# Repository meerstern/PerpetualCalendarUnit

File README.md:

# 万年カレンダーユニット　Perpetual Calendar Unit

## 概要 
  * 2.13インチ、122x250 超低消費電力LCDを用いた万年カレンダーユニットです  
  * 現在の日付、時刻、その月を表示します  
  * 精度±3.8ppmの温度補正機能付RTC SD3077を搭載しています  
  * LCD横のジョイスティックで翌月や前月等、表示月を変更することが可能です  
  * 単三電池2本で約1年前後の電池寿命です  
  * Pico-SDKを使用したソースコードを公開しています  

## 仕様  
  * ジョイスティック(カレンダー切替、時刻合わせ)、BOOTボタン、RESETボタンを搭載しています  
  * マイコンRP2040、RTC SD3077、電源管理IC XC6194を使用しています  
  * RTCのINT信号によって電源管理ICからマイコンを1分に1回、起動させています  
  * 起動後はLCD表示を更新後、シャットダウン信号を電源管理ICに送って、マイコンの電源を切ることで省電力化しています    
  * RTCのINTとジョイスティックの中央ボタンは同一信号となっており、ユーザ操作の長押しによって復帰します  
  * 単三電池2本もしくはUSB電源(USB Type-C)  
  * 時刻(RTC)保持電池 CR1220  
  * サイズ82mm x32mm x 30mm(突起部、USBコネクタ除く)

## 注意点
  * LCDはガラス製のため、強い力や衝撃を与えると破損する可能性があります     
  * 使用時はクリップ等の金属がユニット内に入り込まないように注意してください  
  * 電池寿命は使用環境や使用方法によって大きく変動するため、期間を保証するものではありません  
  * 操作時はジョイスティックの中央を3秒程度長押しして、スリープから復帰させてください  
  * ジョイスティックの応答がない場合は背面のRSTボタンを押してください  
  * 万一、画面端に点表示が残る場合はカレンダー切替等で画面を数回リフレッシュすることで解消します  
  * 告知なしに部品や仕様を変更する場合があります  
  
## 使い方  

### a.通常使用の場合  
 単三電池2個もしくはUSB Type-CをUSB電源等に接続してください  
 画面がすぐに表示されない場合はLCD右横のジョイスティックの中央を3秒程度長押ししてください  
 万一、画面端に点表示が残る場合はカレンダー切替等で画面を数回リフレッシュすることで解消します  

### b.カレンダー切替  
 ジョイスティックの中央を3秒程度長押しして、スリープから復帰させてください  
 スリープから復帰すると画面が一瞬、点滅してLCDが再度、更新されます  
 この状態でジョイスティックを上下に動かすと表示月を切り替えることが可能です  
 10秒以上放置するか、ジョイスティックの中央を再度、押すと現在の月に戻ります  
 万一、ジョイスティックの応答がない場合は背面のRSTボタンを押してください  
　
### c.日付時刻合わせ  
 ジョイスティックの中央を3秒程度長押しして、スリープから復帰させてください  
 スリープから復帰すると画面が一瞬、点滅してLCDが再度、更新されます  
 この状態でジョイスティックを左右どちらかに3秒程度長押しすると日付、時刻合わせモードに入ります  
 左右で設定項目変更、上下で数値を変更します  
 決定する場合ははジョイスティックの中央を押して設定を完了させます  
 万一、ジョイスティックの応答がない場合は背面のRSTボタンを押してください  
    
### d.ファームウェアの書換を行う場合
 PC等にUSB Type-Cを接続し、BOOTボタンを押した状態でRSTボタンを押すとUSBドライブとして認識されます  
 ファームウェアファイル(*.uf2)を認識されたUSBドライブに書き込むことでファームの書換が可能です  
 
## リリースノート
　v1.1 クロックダウンによる更なる省エネ化を実施  
　v1.2 初期状態によってスリープ復帰に失敗する不具合を修正  

## 電池交換時の確認
  * RTC電池は電源供給なしで3年以上、日時、時刻を保持することが可能です  
  * 万一、保持できなくなった場合はCR1220の電池交換を行ってください  
  * 電池交換後は日時、時刻が不定値となるため、必ず時刻、日付を再設定してください  

## 外観

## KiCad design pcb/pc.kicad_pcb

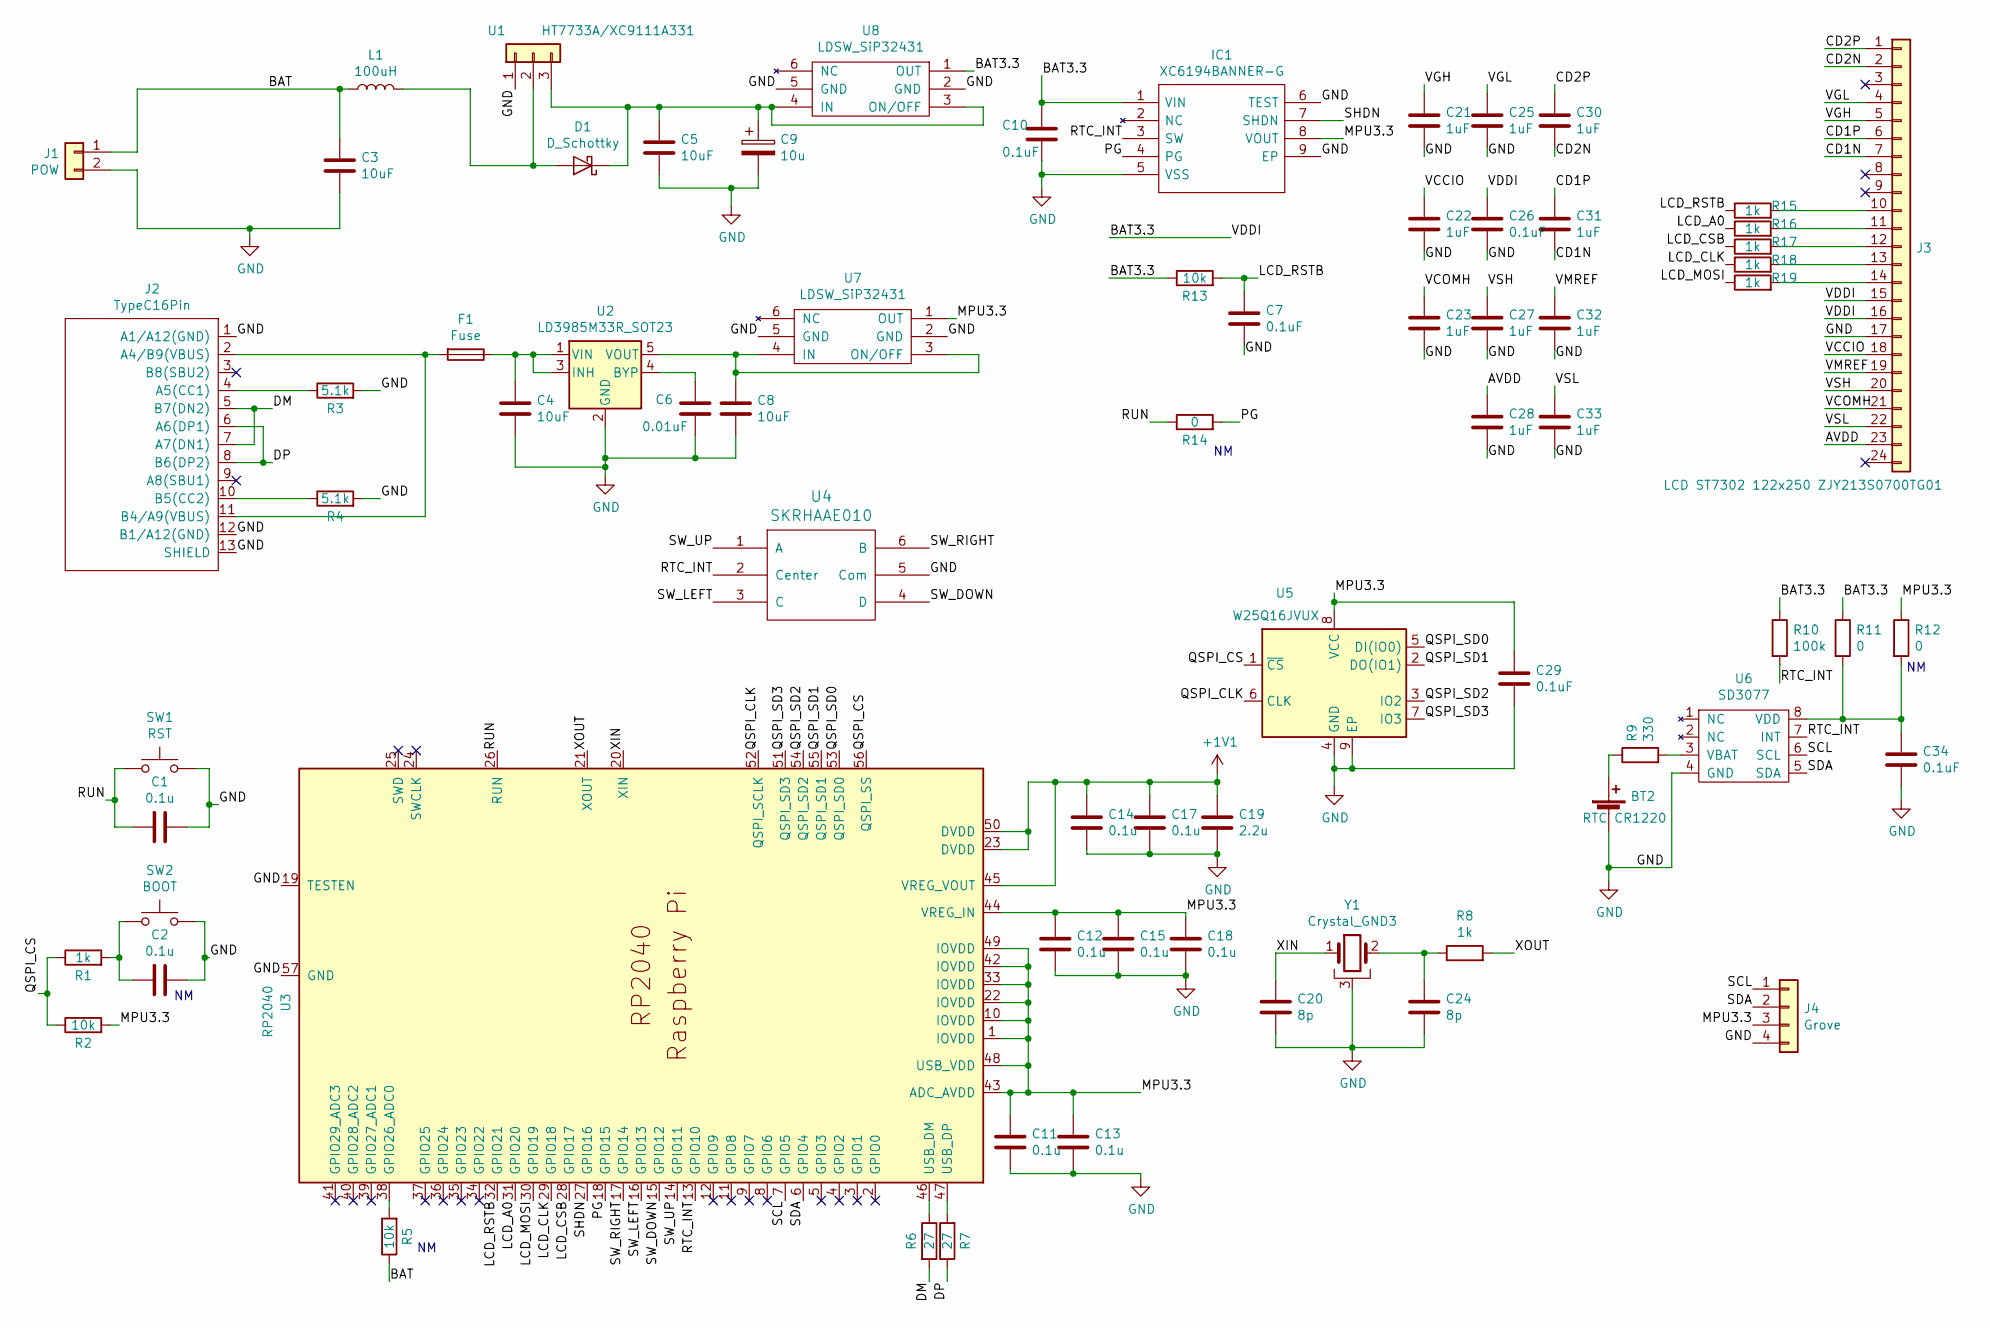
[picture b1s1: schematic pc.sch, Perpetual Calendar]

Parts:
BT2: RTC CR1220; 2895
C1, C2, C11, C12, C13, C14, C15, C17, C18: 0.1u; C_0603_1608Metric
C3, C4, C5, C8: 10uF; C_0805_2012Metric
C6: 0.01uF; C_0603_1608Metric
C7, C10, C26, C29, C34: 0.1uF; C_0603_1608Metric
C9: 10u; CP_Elec_6.3x3
C19: 2.2u; C_0603_1608Metric
C20, C24: 8p; C_0603_1608Metric
C21, C22, C23, C25, C27, C28, C30, C31, C32, C33: 1uF; C_0603_1608Metric
D1: D_Schottky; D_SOD-123
F1: Fuse; Fuse_0603_1608Metric
IC1: XC6194BANNER-G; XC6194BANNERG; Manufacturer_Part_Number XC6194BANNER-G; Mouser Part Number 865-XC6194BANNER-G
J1: POW; JST_PH_B2B-PH-K_1x02_P2.00mm_Vertical
J2: TypeC16Pin; TypeC_16Pin
J3: LCD ST7302 122x250 ZJY213S0700TG01; 24pin0.8mm
J4: Grove; GROVE
L1: 100uH; L_Taiyo-Yuden_MD-5050
R1, R8, R15, R16, R17, R18, R19: 1k; R_0603_1608Metric
R2, R5, R13: 10k; R_0603_1608Metric
R3, R4: 5.1k; R_0603_1608Metric
R6, R7: 27; R_0603_1608Metric
R9: 330; R_0603_1608Metric
R10: 100k; R_0603_1608Metric
R11, R12, R14: 0; R_0603_1608Metric
SW1: RST; SKRPACE010
SW2: BOOT; SKRPACE010
U1: HT7733A/XC9111A331; SOT-23
U2: LD3985M33R_SOT23; SOT-23-5
U3: RP2040; RP2040-QFN-56
U4: SKRHAAE010
U5: W25Q16JVUX; SON-8-1EP_3x2mm_P0.5mm_EP1.4x1.6mm
U6: SD3077; SO-8_5.3x6.2mm_P1.27mm
U7, U8: LDSW_SiP32431; SOT-363_SC-70-6
Y1: Crystal_GND3; FA238V

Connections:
+1V1: C14.1, C17.1, C19.1, U3.23 (DVDD), U3.45 (VREG_VOUT), U3.50 (DVDD)
/AVDD: C28.1, J3.23
/BAT: C3.1, J1.1, L1.1, R5.1
/BAT3.3: C10.1, C26.1, IC1.1 (VIN), J3.15, J3.16, R10.1, R11.1, R13.1, U8.1 (OUT)
/CD1N: C31.2, J3.7
/CD1P: C31.1, J3.6
/CD2N: C30.2, J3.2
/CD2P: C30.1, J3.1
/DM: J2.5 (B7(DN2)), J2.7 (A7(DN1)), R6.2
/DP: J2.6 (A6(DP1)), J2.8 (B6(DP2)), R7.1
/LCD_A0: R16.1, U3.31 (GPIO20)
/LCD_CLK: R18.1, U3.29 (GPIO18)
/LCD_CSB: R17.1, U3.28 (GPIO17)
/LCD_MOSI: R19.1, U3.30 (GPIO19)
/LCD_RSTB: C7.1, R13.2, R15.1, U3.32 (GPIO21)
/MPU3.3: C11.1, C12.1, C13.1, C15.1, C18.1, C29.1, IC1.8 (VOUT), J4.3, R2.2, R12.1, U3.1 (IOVDD), U3.10 (IOVDD), U3.22 (IOVDD), U3.33 (IOVDD), U3.42 (IOVDD), U3.43 (ADC_AVDD), U3.44 (VREG_IN), U3.48 (USB_VDD), U3.49 (IOVDD), U5.8 (VCC), U7.1 (OUT)
/PG: IC1.4 (PG), R14.2, U3.18 (GPIO15)
/QSPI_CLK: U3.52 (QSPI_SCLK), U5.6 (CLK)
/QSPI_CS: R1.1, R2.1, U3.56 (QSPI_SS), U5.1 (~CS)
/QSPI_SD0: U3.53 (QSPI_SD0), U5.5 (DI(IO0))
/QSPI_SD1: U3.55 (QSPI_SD1), U5.2 (DO(IO1))
/QSPI_SD2: U3.54 (QSPI_SD2), U5.3 (IO2)
/QSPI_SD3: U3.51 (QSPI_SD3), U5.7 (IO3)
/RTC_INT: IC1.3 (SW), R10.2, U3.13 (GPIO10), U4.2 (Center), U6.7 (INT)
/RUN: C1.2, R14.1, SW1.1, U3.26 (RUN)
/SCL: J4.1, U3.7 (GPIO5), U6.6 (SCL)
/SDA: J4.2, U3.6 (GPIO4), U6.5 (SDA)
/SHDN: IC1.7 (SHDN), U3.27 (GPIO16)
/SW_DOWN: U3.15 (GPIO12), U4.4 (D)
/SW_LEFT: U3.16 (GPIO13), U4.3 (C)
/SW_RIGHT: U3.17 (GPIO14), U4.6 (B)
/SW_UP: U3.14 (GPIO11), U4.1 (A)
/VCCIO: C22.1, J3.18
/VCOMH: C23.1, J3.21
/VGH: C21.1, J3.5
/VGL: C25.1, J3.4
/VMREF: C32.1, J3.19
/VSH: C27.1, J3.20
/VSL: C33.1, J3.22
/XIN: C20.1, U3.20 (XIN), Y1.1
/XOUT: R8.2, U3.21 (XOUT)
GND: BT2.2 (-), C1.1, C2.1, C3.2, C4.2, C5.2, C6.2, C7.2, C8.2, C9.2, C10.2, C11.2, C12.2, C13.2, C14.2, C15.2, C17.2, C18.2, C19.2, C20.2, C21.2, C22.2, C23.2, C24.2, C25.2, C26.2, C27.2, C28.2, C29.2, C32.2, C33.2, C34.2, IC1.5 (VSS), IC1.6 (TEST), IC1.9 (EP), J1.2, J2.1 (A1/A12(GND)), J2.12 (B1/A12(GND)), J2.13 (SHIELD), J3.17, J4.4, R3.2, R4.2, SW1.2, SW2.2, U1.1, U2.2 (GND), U3.19 (TESTEN), U3.57 (GND), U4.5 (Com), U5.4 (GND), U5.9 (EP), U6.4 (GND), U7.2 (GND), U7.5 (GND), U8.2 (GND), U8.5 (GND), Y1.3
unnamed: BT2.1 (+), R9.1
unnamed: C2.2, R1.2, SW2.1
unnamed: C4.1, F1.1, U2.1 (VIN), U2.3 (INH)
unnamed: C5.1, C9.1, D1.1 (K), U1.3, U8.3 (ON/OFF), U8.4 (IN)
unnamed: C6.1, U2.4 (BYP)
unnamed: C8.1, U2.5 (VOUT), U7.3 (ON/OFF), U7.4 (IN)
unnamed: C24.1, R8.1, Y1.2
unnamed: C34.1, R11.2, R12.2, U6.8 (VDD)
unnamed: D1.2 (A), L1.2, U1.2
unnamed: F1.2, J2.2 (A4/B9(VBUS)), J2.11 (B4/A9(VBUS))
unnamed: J2.4 (A5(CC1)), R3.1
unnamed: J2.10 (B5(CC2)), R4.1
unnamed: J3.10, R15.2
unnamed: J3.11, R16.2
unnamed: J3.12, R17.2
unnamed: J3.13, R18.2
unnamed: J3.14, R19.2
unnamed: R5.2, U3.38 (GPIO26_ADC0)
unnamed: R6.1, U3.46 (USB_DM)
unnamed: R7.2, U3.47 (USB_DP)
unnamed: R9.2, U6.3 (VBAT)

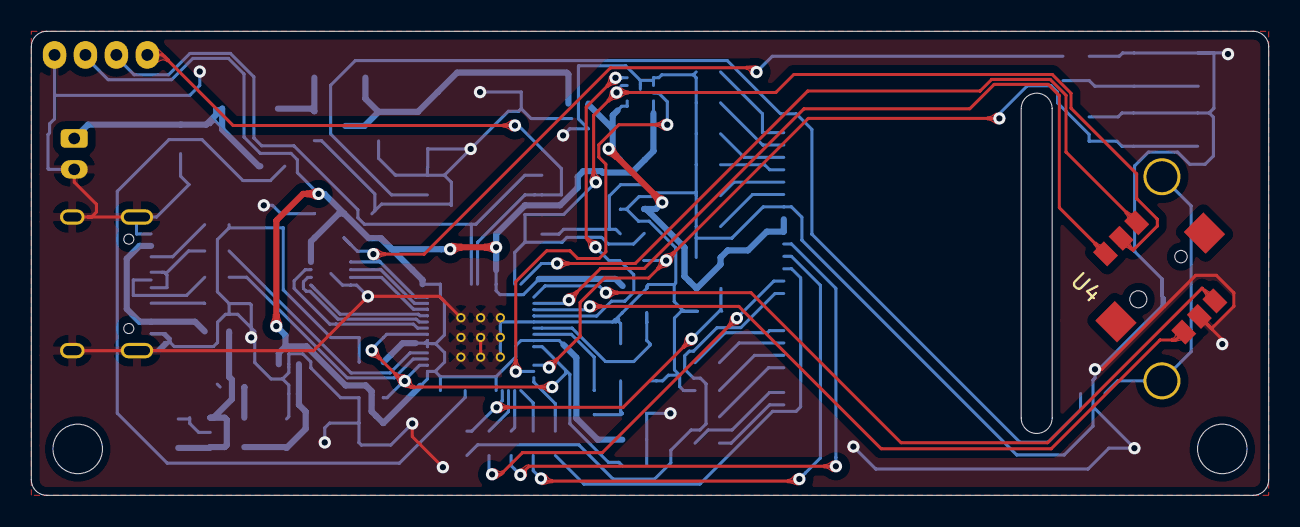
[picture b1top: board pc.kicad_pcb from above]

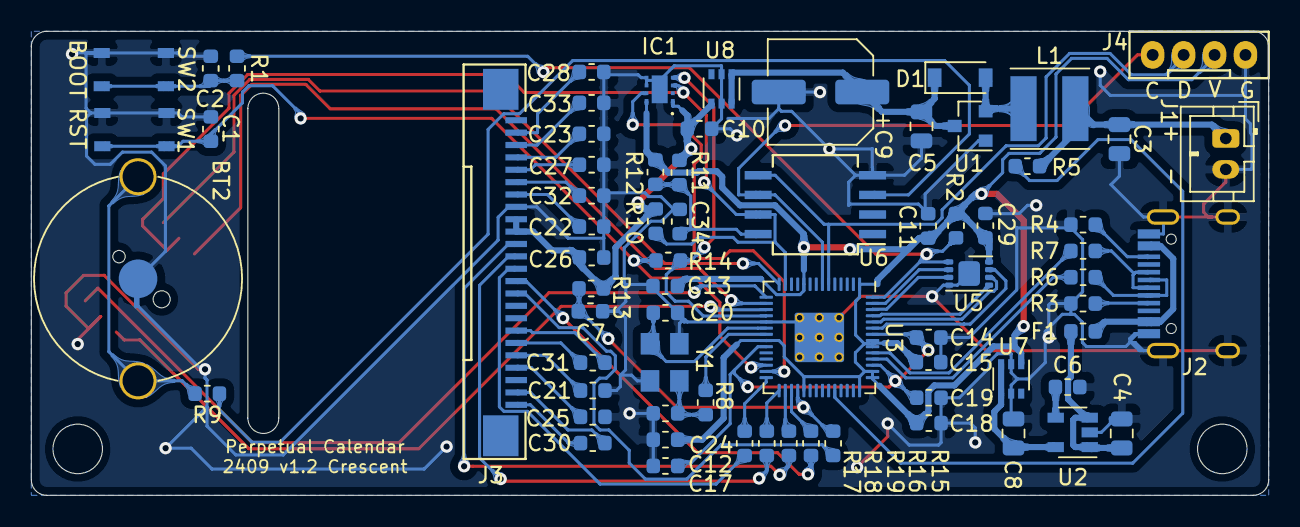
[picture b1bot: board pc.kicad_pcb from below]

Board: 2 copper layers, 80.0 x 30.0 mm, 74 parts (71 on the bottom side), 63 nets.

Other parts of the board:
REF1, REF2: MountingHole_3.2mm_M3

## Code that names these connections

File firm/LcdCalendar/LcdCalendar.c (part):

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	}

	//Check Edit Count	
	if( gpio_get(PIN_SW_LEFT)==0 || gpio_get(PIN_SW_RIGHT)==0)
		editModeCount++;
	else
		editModeCount=0;
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void checkUserInput()
{
	bool hasInput = false;
	uint8_t rtc_int = gpio_get(PIN_RTCINT);
	uint8_t sw_up = gpio_get(PIN_SW_UP);
	uint8_t sw_down = gpio_get(PIN_SW_DOWN);
	uint8_t sw_right = gpio_get(PIN_SW_RIGHT);
	uint8_t sw_left = gpio_get(PIN_SW_LEFT);
	
	if( rtc_int_old == 0 &&  rtc_int == 1 )
	{
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	gpio_pull_up(PIN_RTCINT);

	
	gpio_init(PIN_SW_UP);
	gpio_set_dir(PIN_SW_UP, GPIO_IN);
	gpio_pull_up(PIN_SW_UP);

	
	gpio_init(PIN_SW_DOWN);
	gpio_set_dir(PIN_SW_DOWN, GPIO_IN);
	gpio_pull_up(PIN_SW_DOWN);

	
	gpio_init(PIN_SW_LEFT);
	gpio_set_dir(PIN_SW_LEFT, GPIO_IN);
	gpio_pull_up(PIN_SW_LEFT);

	gpio_init(PIN_SW_RIGHT);
	gpio_set_dir(PIN_SW_RIGHT, GPIO_IN);
	gpio_pull_up(PIN_SW_RIGHT);

	//XC6194 Load Switch Settings
	gpio_init(PIN_SHDN);
	gpio_set_dir(PIN_SHDN, GPIO_OUT);
    gpio_put(PIN_SHDN, 0);

	SoftSpiInit();

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			gpio_init(PIN_RST);
			gpio_set_dir(PIN_RST, GPIO_IN);
			sleep_ms(1);
			gpio_put(PIN_SHDN, 1);//MPU Power Shutdown for Battery
			sleep_ms(10);
			
			//For USB Power Use
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
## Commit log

2024-10-31 Add pcb files
2024-10-31 Add firmware & images
2026-01-28 Fix Update Fail of RTC

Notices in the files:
firm/LcdCalendar/LcdCalendar.c:
Copyright (c) 2024
Released under the MIT license
http://opensource.org/licenses/mit-license.php
